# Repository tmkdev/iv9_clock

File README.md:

# iv9_clock
IV-9 Clock. Targeted at raspberry pi. 

[Video](https://photos.app.goo.gl/XQEr5hhQ3mAr3oM97)

[Completed clock gallery](https://photos.app.goo.gl/mM42fY7hRfecAtkD6)

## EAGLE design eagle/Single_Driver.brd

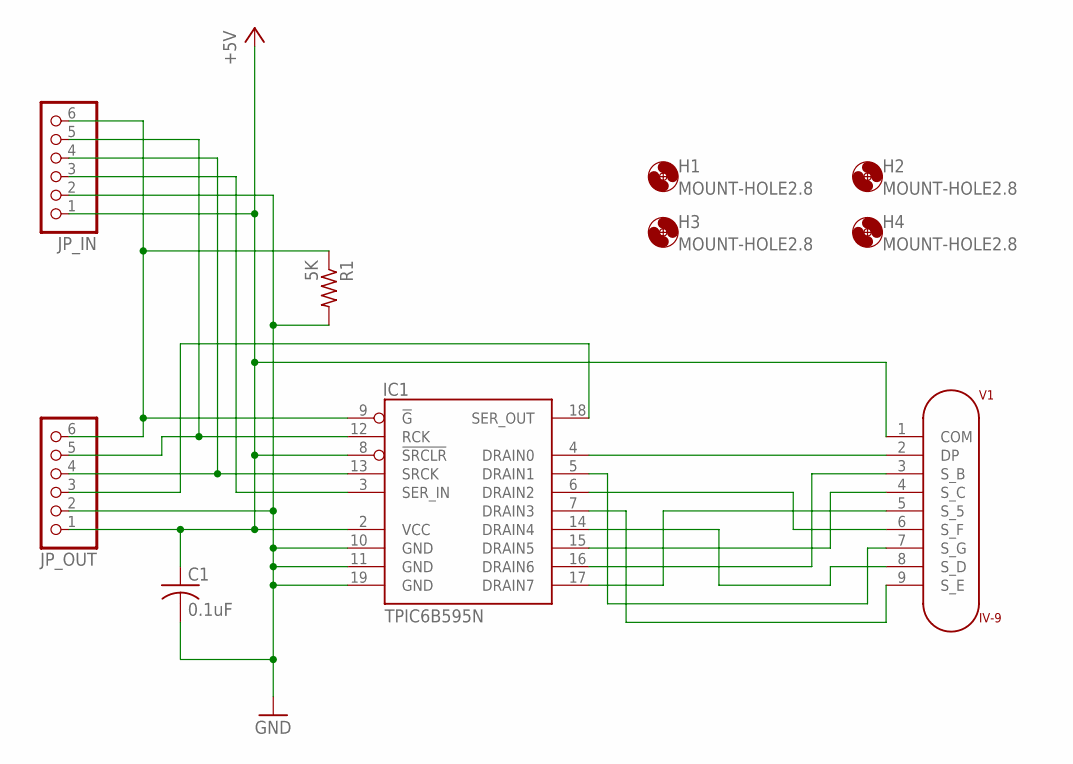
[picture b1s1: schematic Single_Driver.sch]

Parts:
C1: 0.1uF; C025-025X050
H1, H2, H3, H4: MOUNT-HOLE2.8; 2,8
IC1: TPIC6B595N; DIL20
JP_IN: PINHD-1X6; 1X06
JP_OUT: PINHD-1X6; 1X06
R1: 5K; 0207/9
V1: IV-9; TO100

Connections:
+5V: C1.1, IC1.2 (VCC), IC1.8 (!SRCLR), JP_IN.1, JP_OUT.1, V1.1 (COM)
GND: C1.2, IC1.10 (GND), IC1.11 (GND), IC1.19 (GND), JP_IN.2, JP_OUT.2, R1.2
unnamed: IC1.4 (DRAIN0), V1.2 (DP)
unnamed: IC1.16 (DRAIN6), V1.3 (S_B)
unnamed: IC1.15 (DRAIN5), V1.4 (S_C)
unnamed: IC1.17 (DRAIN7), V1.5 (S_5)
unnamed: IC1.6 (DRAIN2), V1.6 (S_F)
unnamed: IC1.7 (DRAIN3), V1.9 (S_E)
unnamed: IC1.14 (DRAIN4), V1.8 (S_D)
unnamed: IC1.5 (DRAIN1), V1.7 (S_G)
unnamed: IC1.9 (!G), JP_IN.6, JP_OUT.6, R1.1
RCLK: IC1.12 (RCK), JP_IN.5, JP_OUT.5
SER_IN: IC1.3 (SER_IN), JP_IN.3
SER_OUT: IC1.18 (SER_OUT), JP_OUT.3
SRCK: IC1.13 (SRCK), JP_IN.4, JP_OUT.4

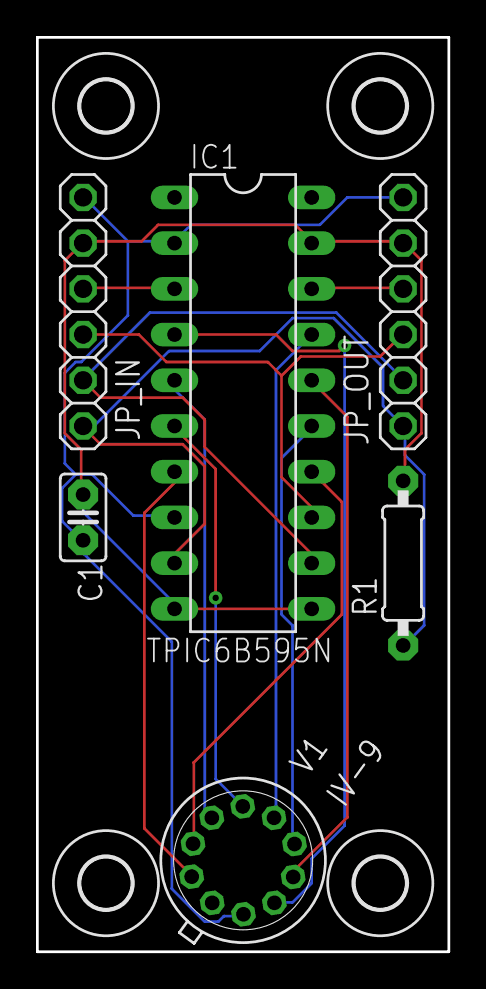
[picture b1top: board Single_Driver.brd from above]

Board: 2 copper layers, 22.9 x 50.8 mm, 10 parts (0 on the bottom side), 15 nets.

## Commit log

2019-03-10 Initia commit'
2019-03-10 Added IV-9 Pin mapps in comments
2019-03-10 Added TPIC to IV-9 mapping in comments.
2019-03-10 Moved comments to the top
2019-03-24 Adding eagle files to project
2019-03-24 Removed pycache.. How did that get in there. Again?
2019-03-24 Ready to test on Raspberry pi..
2019-03-24 Added todo.
2019-03-24 Working on the pi zero.. modified: clock.py modified: shiftregister.py
2019-03-25 Adding the IV-9 Eagle Library
2019-03-25 Added TPIC library too - fond this one somewhere - not mine. IF it's yours let me know and I'll credit you.
2019-03-26 Adding an image..
2019-03-26 Fixed markup
2019-03-26 Really fixed the markdown
2019-03-26 Resized photo..
2019-04-06 Added a single tube tester..
2019-04-09 add video of tube test
2019-07-17 Added seconds marker
2019-07-19 Added completed clock gallery
2019-07-20 Added seconds pulse and a AM/PM indicator. modified: clock.py
2019-07-20 Added args to clock
2019-07-20 Added switches for am/pm milltime and seconds indicator. modified: clock.py
2019-07-21 CAD files
2019-07-21 Added schematic png
